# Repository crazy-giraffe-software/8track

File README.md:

# 8track

A place to keep open-source projects related to my 8-track ~obsession~ hobby.

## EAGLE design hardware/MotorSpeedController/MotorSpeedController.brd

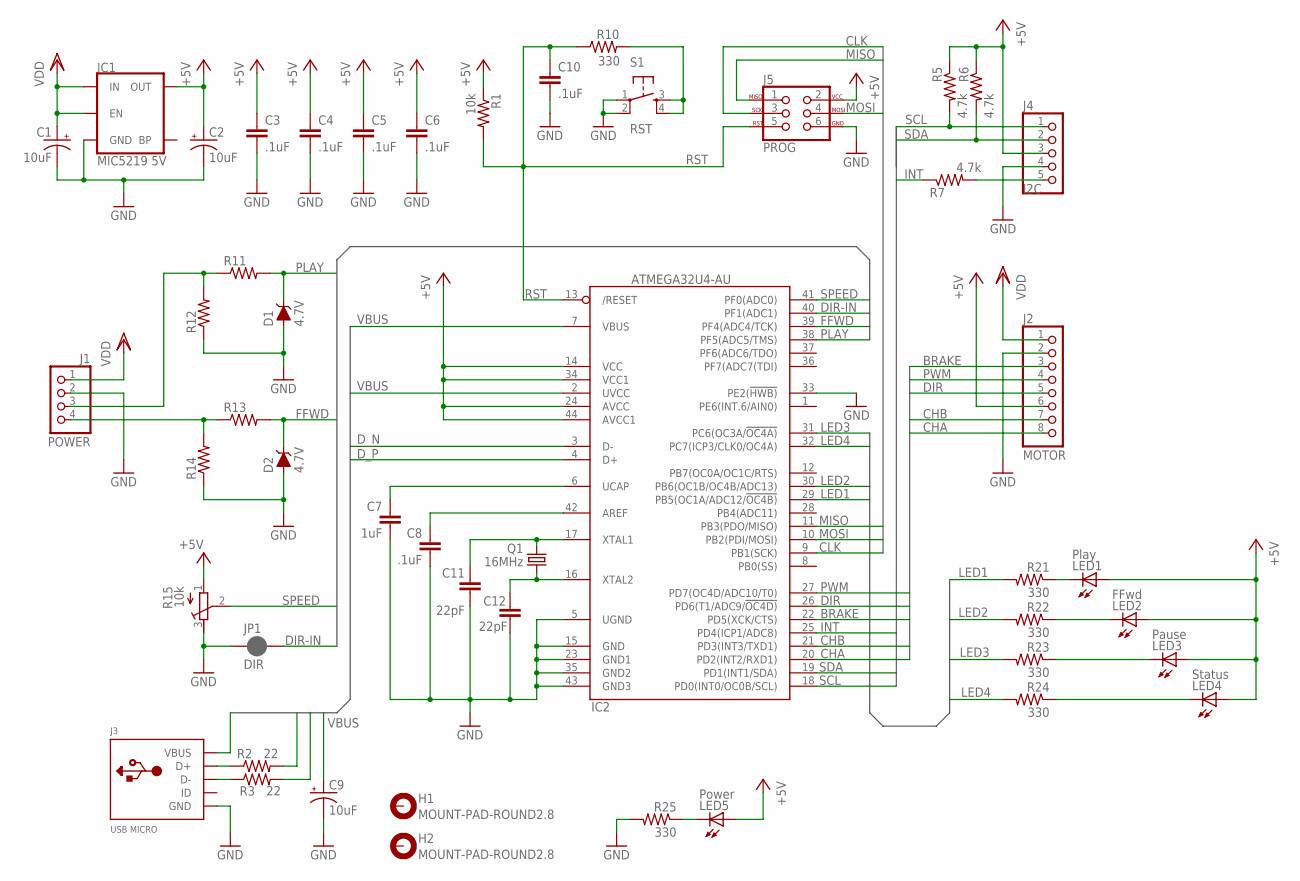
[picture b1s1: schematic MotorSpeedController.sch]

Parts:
C1, C2, C9: 10uF; PANASONIC_B
C3, C4, C5, C6, C8, C10: .1uF; 0603-CAP
C7: 1uF; 0603-CAP
C11, C12: 22pF; 0603
D1, D2: 4.7V; SOD-323
H1, H2: MOUNT-PAD-ROUND2.8; 2,8-PAD
IC1: MIC5219 5V; SOT23-5
IC2: ATMEGA32U4-AU; TQFP44
J1: POWER; 1X04
J2: MOTOR; 1X08
J3: USB MICRO; MICROBUILDER_4UCONN_20329_V2
J4: I2C; 1X05
J5: PROG; 2X3
JP1: DIR; SMT-JUMPER_2_NC_PASTE_SILK
LED1: Play; LED-0603
LED2: FFwd; LED-0603
LED3: Pause; LED-0603
LED4: Status; LED-0603
LED5: Power; LED-0603
Q1: 16MHz; HC49/S
R1: 10k; 0603-RES
R2, R3: 22; 0603-RES
R5, R6, R7: 4.7k; R0603
R10, R21, R22, R23, R24, R25: 330; 0603-RES
R11, R12, R13, R14: R-US_R0603; R0603
R15: 10k; RTRIM3296W
S1: RST; TACTILE_SWITCH_SMD

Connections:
+5V: C2.+, C3.1, C4.1, C5.1, C6.1, IC1.5 (OUT), IC2.14 (VCC), IC2.24 (AVCC), IC2.34 (VCC1), IC2.44 (AVCC1), J2.6, J4.3, J5.2, LED1.A, LED2.A, LED3.A, LED4.A, LED5.A, R1.1, R5.1, R6.1, R15.1 (A)
+PWR: C1.+, IC1.1 (IN), IC1.3 (EN), J1.1, J2.1
BRAKE: IC2.22 (PD5(XCK/CTS)), J2.3
CD_N: J3.D-, R3.1
CD_P: J3.D+, R2.1
CHA: IC2.20 (PD2(INT2/RXD1)), J2.8
CHB: IC2.21 (PD3(INT3/TXD1)), J2.7
CLK: IC2.9 (PB1(SCK)), J5.3
DIR: IC2.26 (PD6(T1/ADC9/!OC4D)), J2.5
DIR-IN: IC2.40 (PF1(ADC1)), JP1.2
D_N: IC2.3 (D-), R3.2
D_P: IC2.4 (D+), R2.2
FFWD: D2.C, IC2.39 (PF4(ADC4/TCK)), R13.2
GND: C1.-, C2.-, C3.2, C4.2, C5.2, C6.2, C7.2, C8.2, C9.-, C10.2, C11.2, C12.2, D1.A, D2.A, IC1.2 (GND), IC2.5 (UGND), IC2.15 (GND), IC2.23 (GND1), IC2.33 (PE2(!HWB)), IC2.35 (GND2), IC2.43 (GND3), J1.2, J2.2, J3.BASE@1 (GND), J3.BASE@2 (GND), J3.GND, J3.SPRT@1 (GND), J3.SPRT@2 (GND), J3.SPRT@3 (GND), J3.SPRT@4 (GND), J4.4, J5.6, JP1.1, R12.1, R14.1, R15.3 (E), R25.2, S1.1, S1.2
INT: IC2.25 (PD4(ICP1/ADC8)), R7.1
LED1: IC2.29 (PB5(OC1A/ADC12/!OC4B)), R21.2
LED2: IC2.30 (PB6(OC1B/OC4B/ADC13)), R22.2
LED3: IC2.31 (PC6(OC3A/!OC4A)), R23.2
LED4: IC2.32 (PC7(ICP3/CLK0/OC4A)), R24.2
MISO: IC2.11 (PB3(PDO/MISO)), J5.1
MOSI: IC2.10 (PB2(PDI/MOSI)), J5.4
unnamed: LED3.C, R23.1
unnamed: C8.1, IC2.42 (AREF)
unnamed: C11.1, IC2.17 (XTAL1), Q1.2
unnamed: R10.2, S1.3, S1.4
unnamed: C7.1, IC2.6 (UCAP)
unnamed: LED4.C, R24.1
unnamed: C12.1, IC2.16 (XTAL2), Q1.1
unnamed: J4.5, R7.2
unnamed: J1.4, R13.1, R14.2
unnamed: LED5.C, R25.1
unnamed: J1.3, R11.1, R12.2
unnamed: LED1.C, R21.1
PLAY: D1.C, IC2.38 (PF5(ADC5/TMS)), R11.2
PWM: IC2.27 (PD7(OC4D/ADC10/T0)), J2.4
R22: LED2.C, R22.1
RST: C10.1, IC2.13 (/RESET), J5.5, R1.2, R10.1
SCL: IC2.18 (PD0(INT0/OC0B/SCL)), J4.1, R5.2
SDA: IC2.19 (PD1(INT1/SDA)), J4.2, R6.2
SPEED: IC2.41 (PF0(ADC0)), R15.2 (S)
VBUS: C9.+, IC2.2 (UVCC), IC2.7 (VBUS), J3.VBUS

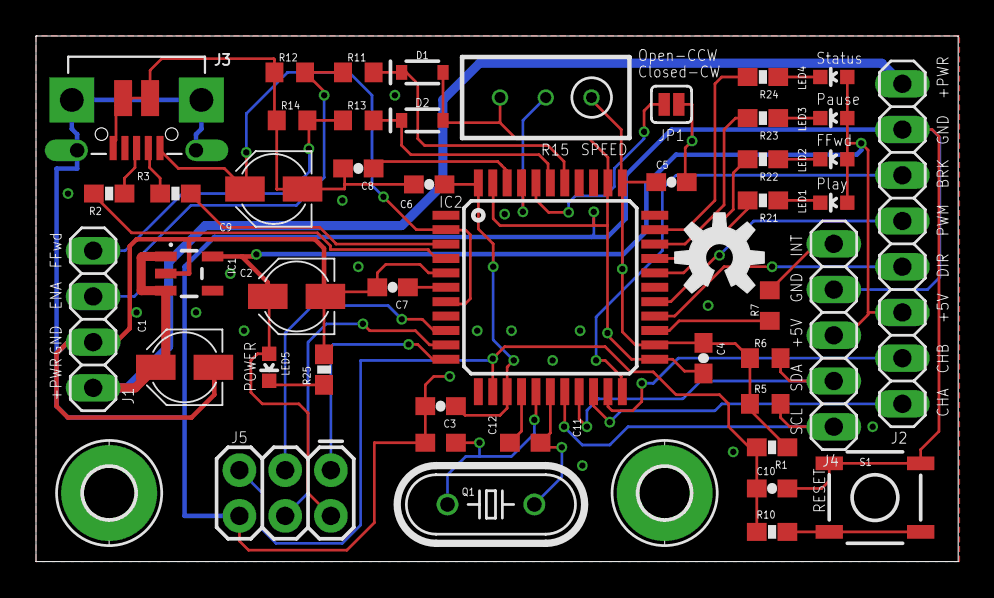
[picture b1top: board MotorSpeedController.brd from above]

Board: 2 copper layers, 51.2 x 29.2 mm, 50 parts (1 on the bottom side), 41 nets.

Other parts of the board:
U$1: OSHW-LOGO-M
U$2: OSHW-LOGO-S

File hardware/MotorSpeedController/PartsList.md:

# Partlist

Part |    Value           | Device                          | Package                      |  Library
---- | ------------------ | ------------------------------- | ---------------------------- | ----------------------------
C1   |   10uF             | CPOL-USB                        | PANASONIC_B                  | rcl
C2   |   10uF             | CPOL-USB                        | PANASONIC_B                  | rcl
C3   |   .1uF             | CAP0603-CAP                     | 0603-CAP                     | SparkFun-Passives
C4   |   .1uF             | CAP0603-CAP                     | 0603-CAP                     | SparkFun-Passives
C5   |   .1uF             | CAP0603-CAP                     | 0603-CAP                     | SparkFun-Passives
C6   |   .1uF             | CAP0603-CAP                     | 0603-CAP                     | SparkFun-Passives
C7   |   1uF              | CAP0603-CAP                     | 0603-CAP                     | SparkFun-Passives
C8   |   .1uF             | CAP0603-CAP                     | 0603-CAP                     | SparkFun-Passives
C9   |   10uF             | CPOL-USB                        | PANASONIC_B                  | rcl
C10  |   .1uF             | CAP0603-CAP                     | 0603-CAP                     | SparkFun-Passives
C11  |   22pF             | 22PF-0603-50V-5%                | 0603                         | SparkFun-Capacitors
C12  |   22pF             | 22PF-0603-50V-5%                | 0603                         | SparkFun-Capacitors
D1   |   4.7V             | DIODE-ZENER-BZT52C3V6S          | SOD-323                      | SparkFun-DiscreteSemi
D2   |   4.7V             | DIODE-ZENER-BZT52C3V6S          | SOD-323                      | SparkFun-DiscreteSemi
IC1  |   MIC5219 5V       | V_REG_MIC52195V                 | SOT23-5                      | SparkFun-IC-Power
IC2  |   ATMEGA32U4-AU    | ATMEGA32U4-AU                   | TQFP44                       | adafruit
J3   |   USB MICRO        | MICROBUILDER_USB_MICRO_20329_V2 | MICROBUILDER_4UCONN_20329_V2 | CrazyGiraffe-MotorSpeedController
J4   |   I2C              | PINHD-1X5                       | 1X05                         | pinhead
J5   |   PROG             | AVR_SPI_PROG_3X2PTH             | 2X3                          | SparkFun
LED1 |   Play             | LED0603                         | LED-0603                     | SparkFun-LED
LED2 |   FFwd             | LED0603                         | LED-0603                     | SparkFun-LED
LED3 |   Pause            | LED0603                         | LED-0603                     | SparkFun-LED
LED4 |   Status           | LED0603                         | LED-0603                     | SparkFun-LED
LED5 |   Power            | LED0603                         | LED-0603                     | SparkFun-LED
Q1   |   16MHz            | CRYSTALHC49S                    | HC49/S                       | adafruit
R1   |   10k              | RESISTOR0603-RES                | 0603-RES                     | SparkFun-Passives
R2   |   22               | RESISTOR0603-RES                | 0603-RES                     | SparkFun-Passives
R3   |   22               | RESISTOR0603-RES                | 0603-RES                     | SparkFun-Passives
R5   |   4.7k             | R-US_R0603                      | R0603                        | rcl
R6   |   4.7k             | R-US_R0603                      | R0603                        | rcl
R7   |   4.7k             | R-US_R0603                      | R0603                        | rcl
R10  |   330              | RESISTOR0603-RES                | 0603-RES                     | SparkFun-Passives
R11  |                    | R-US_R0603                      | R0603                        | rcl
R12  |                    | R-US_R0603                      | R0603                        | rcl
R13  |                    | R-US_R0603                      | R0603                        | rcl
R14  |                    | R-US_R0603                      | R0603                        | rcl
R15  |   10k              | R-TRIMM3296W                    | RTRIM3296W                   | rcl
R21  |   330              | RESISTOR0603-RES                | 0603-RES                     | SparkFun-Passives
R22  |   330              | RESISTOR0603-RES                | 0603-RES                     | SparkFun-Passives
R23  |   330              | RESISTOR0603-RES                | 0603-RES                     | SparkFun-Passives
R24  |   330              | RESISTOR0603-RES                | 0603-RES                     | SparkFun-Passives
R25  |   330              | RESISTOR0603-RES                | 0603-RES                     | SparkFun-Passives
S1   |   RST              | TAC_SWITCHSMD                   | TACTILE_SWITCH_SMD           | SparkFun-Electromechanical

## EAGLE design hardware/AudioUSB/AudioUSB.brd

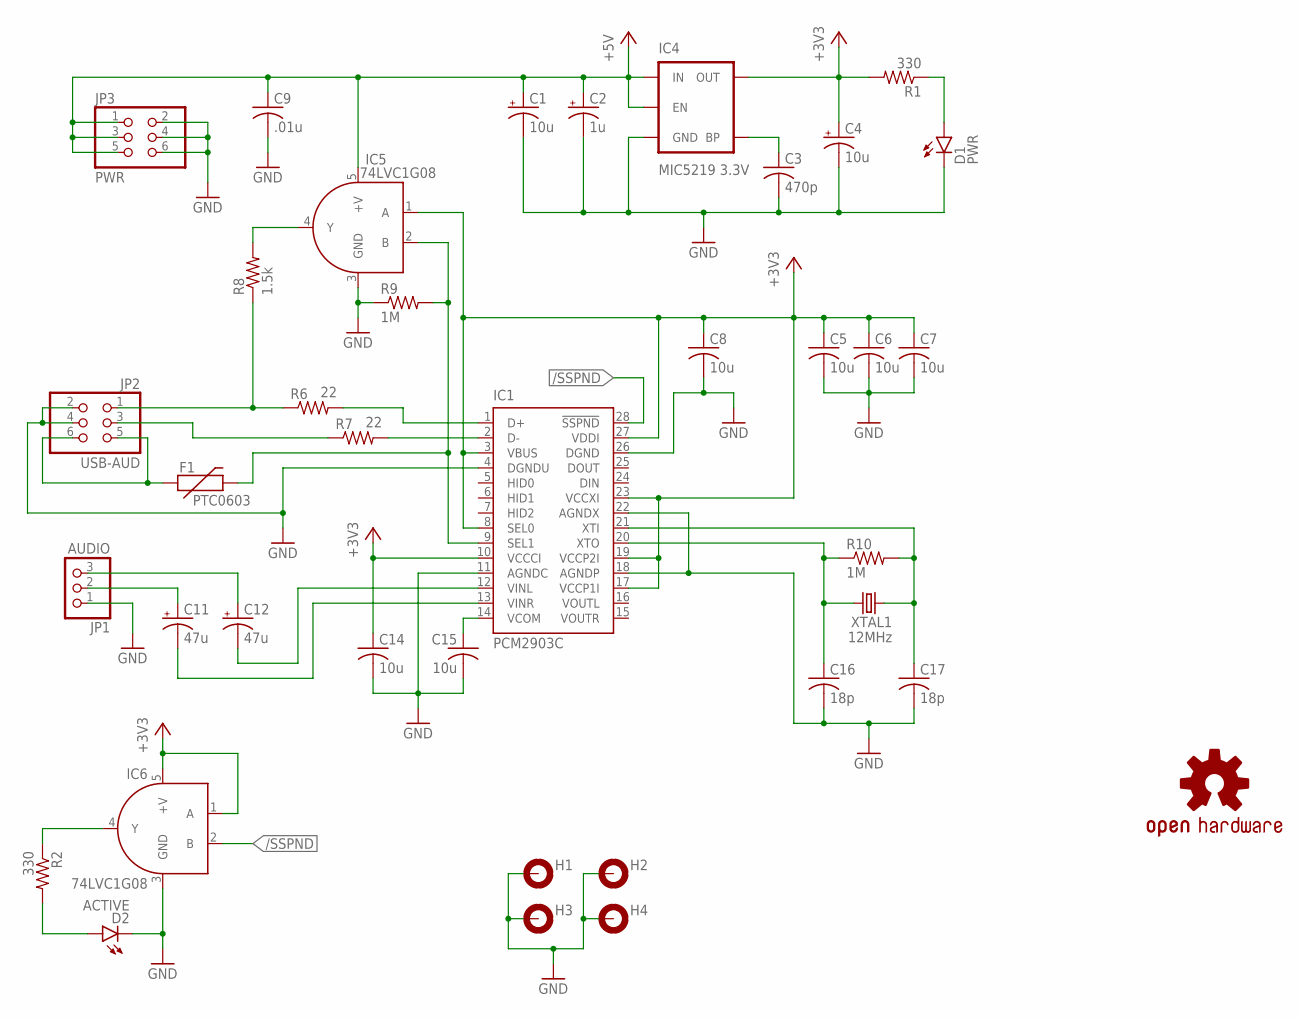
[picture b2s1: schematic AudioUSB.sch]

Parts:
C1, C4: 10u; PANASONIC_B
C2: 1u; PANASONIC_B
C3: 470p; C0603
C5, C6, C7, C8, C14, C15: 10u; C0603
C9: .01u; C0603
C11, C12: 47u; PANASONIC_D
C16, C17: 18p; C0603
D1: PWR; LED-0603
D2: ACTIVE; LED-0603
F1: PTC0603; 0603
H1, H2, H3, H4: MOUNT-PAD-ROUND2.8; 2,8-PAD
IC1: PCM2903C; SSOP28
IC4: MIC5219 3.3V; SOT23-5
IC5, IC6: 74LVC1G08; SOT23-5
JP1: AUDIO; 1X03; DIGIKEY ED10562-ND
JP2: USB-AUD; 2X03
JP3: PWR; 2X03
LOGO1: OSHW-LOGOS; OSHW-LOGO-S
R1, R2: 330; R0603
R6, R7: 22; R0603
R8: 1.5k; R0603
R9, R10: 1M; R0603
XTAL1: 12MHz; HC49US

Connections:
+3V3: C4.+, C5.1, C6.1, C7.1, C8.1, C14.1, IC1.3 (VBUS), IC1.8 (SEL0), IC1.10 (VCCCI), IC1.17 (VCCP1I), IC1.19 (VCCP2I), IC1.23 (VCCXI), IC1.27 (VDDI), IC4.5 (OUT), IC5.1 (A), IC6.1 (A), IC6.5 (+V), R1.2
+5V: C1.+, C2.+, C9.1, IC4.1 (IN), IC4.3 (EN), IC5.5 (+V), JP3.1, JP3.3, JP3.5
/SSPND: IC1.28 (!SSPND), IC6.2 (B)
GND: C1.-, C2.-, C3.2, C4.-, C5.2, C6.2, C7.2, C8.2, C9.2, C14.2, C15.2, C16.2, C17.2, D1.C, D2.C, H1.B2,8, H2.B2,8, H3.B2,8, H4.B2,8, IC1.4 (DGNDU), IC1.11 (AGNDC), IC1.18 (AGNDP), IC1.22 (AGNDX), IC1.26 (DGND), IC4.2 (GND), IC5.3 (GND), IC6.3 (GND), JP1.1, JP2.2, JP2.4, JP3.2, JP3.4, JP3.6, R9.1
GND1: IC6.4 (Y), R2.1
unnamed: C12.-, IC1.12 (VINL)
unnamed: C11.-, IC1.13 (VINR)
unnamed: D1.A, R1.1
unnamed: C11.+, JP1.2
unnamed: C12.+, JP1.3
unnamed: IC5.4 (Y), R8.2
unnamed: JP2.3, R7.1
unnamed: JP2.1, R6.1, R8.1
unnamed: F1.1, JP2.5, JP2.6
unnamed: C16.1, IC1.20 (XTO), R10.1, XTAL1.1
unnamed: IC1.1 (D+), R6.2
unnamed: C17.1, IC1.21 (XTI), R10.2, XTAL1.2
unnamed: IC1.2 (D-), R7.2
unnamed: D2.A, R2.2
unnamed: C3.1, IC4.4 (BP)
unnamed: C15.1, IC1.14 (VCOM)
unnamed: F1.2, IC1.9 (SEL1), IC5.2 (B), R9.2

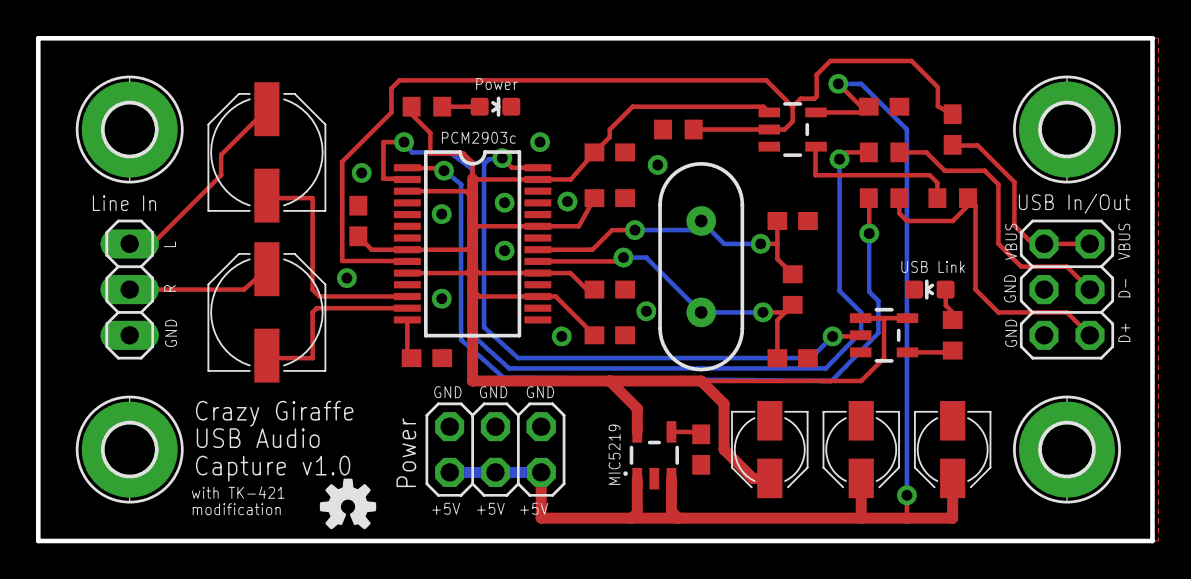
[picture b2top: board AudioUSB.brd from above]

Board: 2 copper layers, 61.9 x 27.9 mm, 38 parts (0 on the bottom side), 22 nets.

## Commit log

2019-05-27 Set theme jekyll-theme-midnight
2019-05-27 Add PCB V1.
2019-05-27 Add custom library.
2019-05-27 Add Audio USB board. Refactored directories.
2019-05-27 Add I2C interrupt/IO.
2019-05-27 Add explanation of I2C pinout.
2019-06-02 Change footprints to match ordered parts. Put some space between crystal and ICSP. Increase clearance on PWR trace.
2020-05-31 Add AudioIdentification code.
2020-06-02 Add AudioIdentification.AcoustID code.
2020-06-02 Add test for AddSample with null.
2020-06-02 Sparky/audio identification (#5)
    * Add AudioIdentification code.
    * Add test for AddSample with null.
2020-06-02 Add parts & BOM. Add PDF schematic. Update .gitignore.
2020-06-02 Add parts & BOM. (#9)
    Add PDF schematic.
    Update .gitignore.
2020-06-12 Add audio identification proxy to run audio identification as a background task. This was originally developed when I was using the GraceNote Win8Phone SDK which had a habit of crashing the process. 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
2020-06-12 Add audio identification proxy to run audio identification as a background task. (#10)
    This was originally developed when I was using the GraceNote Win8Phone SDK which
    had a habit of crashing the process. So I moved it to a background process, i.e. app
    service, and was able to get it working well. Might as well keep it.
2020-06-13 Add audio capture pipeline.
2022-06-22 Bump Newtonsoft.Json
    Bumps [Newtonsoft.Json](https://github.com/JamesNK/Newtonsoft.Json) from 12.0.3 to 13.0.1.
    - [Release notes](https://github.com/JamesNK/Newtonsoft.Json/releases)
    - [Commits](https://github.com/JamesNK/Newtonsoft.Json/compare/12.0.3...13.0.1)
    ---
    updated-dependencies:
    - dependency-name: Newtonsoft.Json
2022-06-22 Bump Newtonsoft.Json in /software/server/AudioIdentification.Proxy
    Bumps [Newtonsoft.Json](https://github.com/JamesNK/Newtonsoft.Json) from 12.0.3 to 13.0.1.
    - [Release notes](https://github.com/JamesNK/Newtonsoft.Json/releases)
    - [Commits](https://github.com/JamesNK/Newtonsoft.Json/compare/12.0.3...13.0.1)
    ---
    updated-dependencies:
    - dependency-name: Newtonsoft.Json
2022-06-23 Bump Newtonsoft.Json in /software/server/AudioIdentification.UnitTests
    Bumps [Newtonsoft.Json](https://github.com/JamesNK/Newtonsoft.Json) from 12.0.3 to 13.0.1.
    - [Release notes](https://github.com/JamesNK/Newtonsoft.Json/releases)
    - [Commits](https://github.com/JamesNK/Newtonsoft.Json/compare/12.0.3...13.0.1)
    ---
    updated-dependencies:
    - dependency-name: Newtonsoft.Json
2022-12-08 Bump Newtonsoft.Json
    Bumps [Newtonsoft.Json](https://github.com/JamesNK/Newtonsoft.Json) from 12.0.3 to 13.0.2.
    - [Release notes](https://github.com/JamesNK/Newtonsoft.Json/releases)
    - [Commits](https://github.com/JamesNK/Newtonsoft.Json/compare/12.0.3...13.0.2)
    ---
    updated-dependencies:
    - dependency-name: Newtonsoft.Json
2022-12-08 Bump Newtonsoft.Json in /software/server/AudioIdentification.UnitTests
    Bumps [Newtonsoft.Json](https://github.com/JamesNK/Newtonsoft.Json) from 12.0.3 to 13.0.2.
    - [Release notes](https://github.com/JamesNK/Newtonsoft.Json/releases)
    - [Commits](https://github.com/JamesNK/Newtonsoft.Json/compare/12.0.3...13.0.2)
    ---
    updated-dependencies:
    - dependency-name: Newtonsoft.Json
2022-12-08 Bump Newtonsoft.Json in /software/server/AudioIdentification.Proxy
    Bumps [Newtonsoft.Json](https://github.com/JamesNK/Newtonsoft.Json) from 12.0.3 to 13.0.2.
    - [Release notes](https://github.com/JamesNK/Newtonsoft.Json/releases)
    - [Commits](https://github.com/JamesNK/Newtonsoft.Json/compare/12.0.3...13.0.2)
    ---
    updated-dependencies:
    - dependency-name: Newtonsoft.Json

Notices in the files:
parts and their libraries:
SparkFun-Aesthetics: Licensing: Creative Commons ShareAlike 4.0 International - https://creativecommons.org/licenses/by-sa/4.0
SparkFun-Electromechanical: Licensing: CC v3.0 Share-Alike You are welcome to use this library for commercial purposes.
